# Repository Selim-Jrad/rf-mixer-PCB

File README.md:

**RF Mixer PCB:**

A Radio Frequency (RF 0.01MHz-4GHz) mixer printed circuit board designed in KiCad.
Using the LT5560 ic (low power, high performance active mixer)
**📋 Project Overview**

This repository contains the design files for an RF mixer PCB, including schematic and layout files compatible with KiCad. The board is designed to handle RF signal mixing applications with proper grounding, filtering, and signal integrity considerations.

***circuit schematics***

***PCB Layout***

***3D Model***

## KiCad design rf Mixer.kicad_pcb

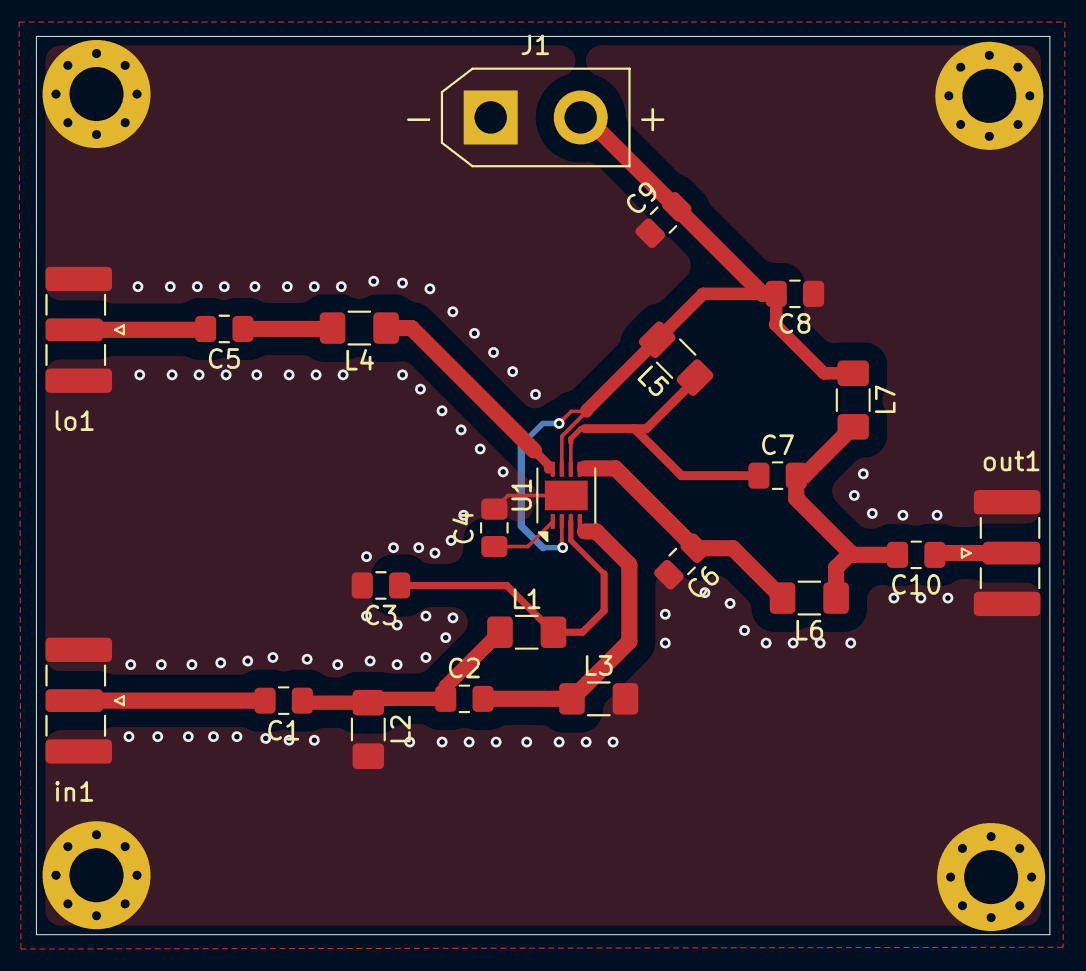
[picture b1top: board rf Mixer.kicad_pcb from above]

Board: 2 copper layers, 56.3 x 49.9 mm, 26 parts (0 on the bottom side), 14 nets.

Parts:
C1, C4, C5: 100pF; C_0805_2012Metric_Pad1.18x1.45mm_HandSolder
C2, C3, C6, C7: 4.7pF; C_0805_2012Metric_Pad1.18x1.45mm_HandSolder
C8, C9: 1µF; C_0805_2012Metric_Pad1.18x1.45mm_HandSolder
C10: 33pF; C_0805_2012Metric_Pad1.18x1.45mm_HandSolder
H1, H2, H3, H4: MountingHole_Pad; MountingHole_3mm_Pad_Via
J1: Conn_01x02_Socket; AMASS_XT30UPB-F_1x02_P5.0mm_Vertical
L1, L3: 6.8nH; L_1206_3216Metric_Pad1.42x1.75mm_HandSolder
L2, L4: 15nH; L_1206_3216Metric_Pad1.42x1.75mm_HandSolder
L5, L6, L7: 270nH; L_1206_3216Metric_Pad1.42x1.75mm_HandSolder
U1: LT5560; DFN-8-1EP_3x3mm_P0.5mm_EP1.65x2.38mm
in1: Conn_Coaxial_Small; SMA_Samtec_SMA-J-P-H-ST-EM1_EdgeMount
lo1: Conn_Coaxial_Small; SMA_Samtec_SMA-J-P-H-ST-EM1_EdgeMount
out1: Conn_Coaxial_Small; SMA_Samtec_SMA-J-P-H-ST-EM1_EdgeMount

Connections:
+5V: C8.2, C9.2, J1.2, L5.2, L7.1, U1.2 (EN), U1.7 (VCC)
GND: C3.2, C4.2, C6.2, C8.1, C9.1, H1.1, H2.1, H3.1, H4.1, J1.1, L2.2, L3.2, U1.9 (PGND), in1.2 (Ext), lo1.2 (Ext), out1.2 (Ext)
unnamed: C1.1, C2.1, L1.1, L2.1
unnamed: C5.1, L4.2
unnamed: C7.2, C10.2, L6.1, L7.2
unnamed: C3.1, L1.2, U1.3 (IN+)
unnamed: C2.2, L3.1, U1.4 (IN-)
unnamed: L4.1, U1.8 (LO+)
unnamed: C4.1, U1.1 (LO-)
unnamed: C7.1, L5.1, U1.6 (OUT+)
unnamed: C6.1, L6.2, U1.5 (OUT-)
unnamed: C1.2, in1.1 (In)
unnamed: C5.2, lo1.1 (In)
unnamed: C10.1, out1.1 (In)
